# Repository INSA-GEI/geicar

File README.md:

# GeiCar Project

The GeiCar project is a project carried out by students at [INSA Toulouse](http://www.insa-toulouse.fr/fr/index.html). This project consists in developing the software of a autonomous car in order to carry out different missions. Several projects are exposed on the [official website] (https://sites.google.com/site/projetsecinsa/).

This repository is intended to provide a basis for students starting a new project on the GeiCar. The present code as well as the documentation is the result of internship carried out by [Alexis24](https://github.com/Alexix24) (Alexis Pierre Dit Lambert)

The platform is developped and maintained by :

* DI MERCURIO Sébastien
* LOMBARD Emmanuel
* MARTIN José

The projects are (or were) surpervised by:

* CHANTHERY Elodie
* DELAUTIER Sébastien
* MONTEIL Thierry
* LE BOTLAN Didier
* AURIOL Guillaume
* DI MERCURIO Sébastien

## Quick User Guide
###Turn the car on and off
* To turn on the car:
  * Toggle the red button to bring the power.
  * Press the START push button (hold it down for a short while).
  * Wait until Raspberry boot up and connect to it using its IP address (written on the board): `ssh pi@10.105.1.xx`
  * When connected start ROS subsystem using :`ros2 launch geicar_start geicar.launch.py`
  * Then, you will get a report of subsystems and be able to control the car using XBOX controler 

* To turn off the car:
	* Use the red button as a switch to turn off the power.

###Use of this repository
* First of all, [fork this repository](https://docs.github.com/en/get-started/quickstart/fork-a-repo) to get yours.
* Then, clone your fresh and new repository on your computer: `git clone https://github.com/<your id>/<your wonderful repo>`
* Have a look in "general" directory for how to connect and work with your car
* For more 'in depth' documentation on a particular subsystem, have a look in following directories:
    * raspberryPI3: Everything about raspberry setup
    * nucleoL476: Stuff about GPS-RTK and IMU
    * nucleoF103: informations on motors control, main power and ultrasonics sensors
    * jetsonNano: Directory containing info on IA, Camera and Lidar
    * simulation: if you want to setup a carla simulation environment

__warning__
You normally do not need to change firmware running in F103 and F476 boards. You main work is on the raspberry and jetson side.

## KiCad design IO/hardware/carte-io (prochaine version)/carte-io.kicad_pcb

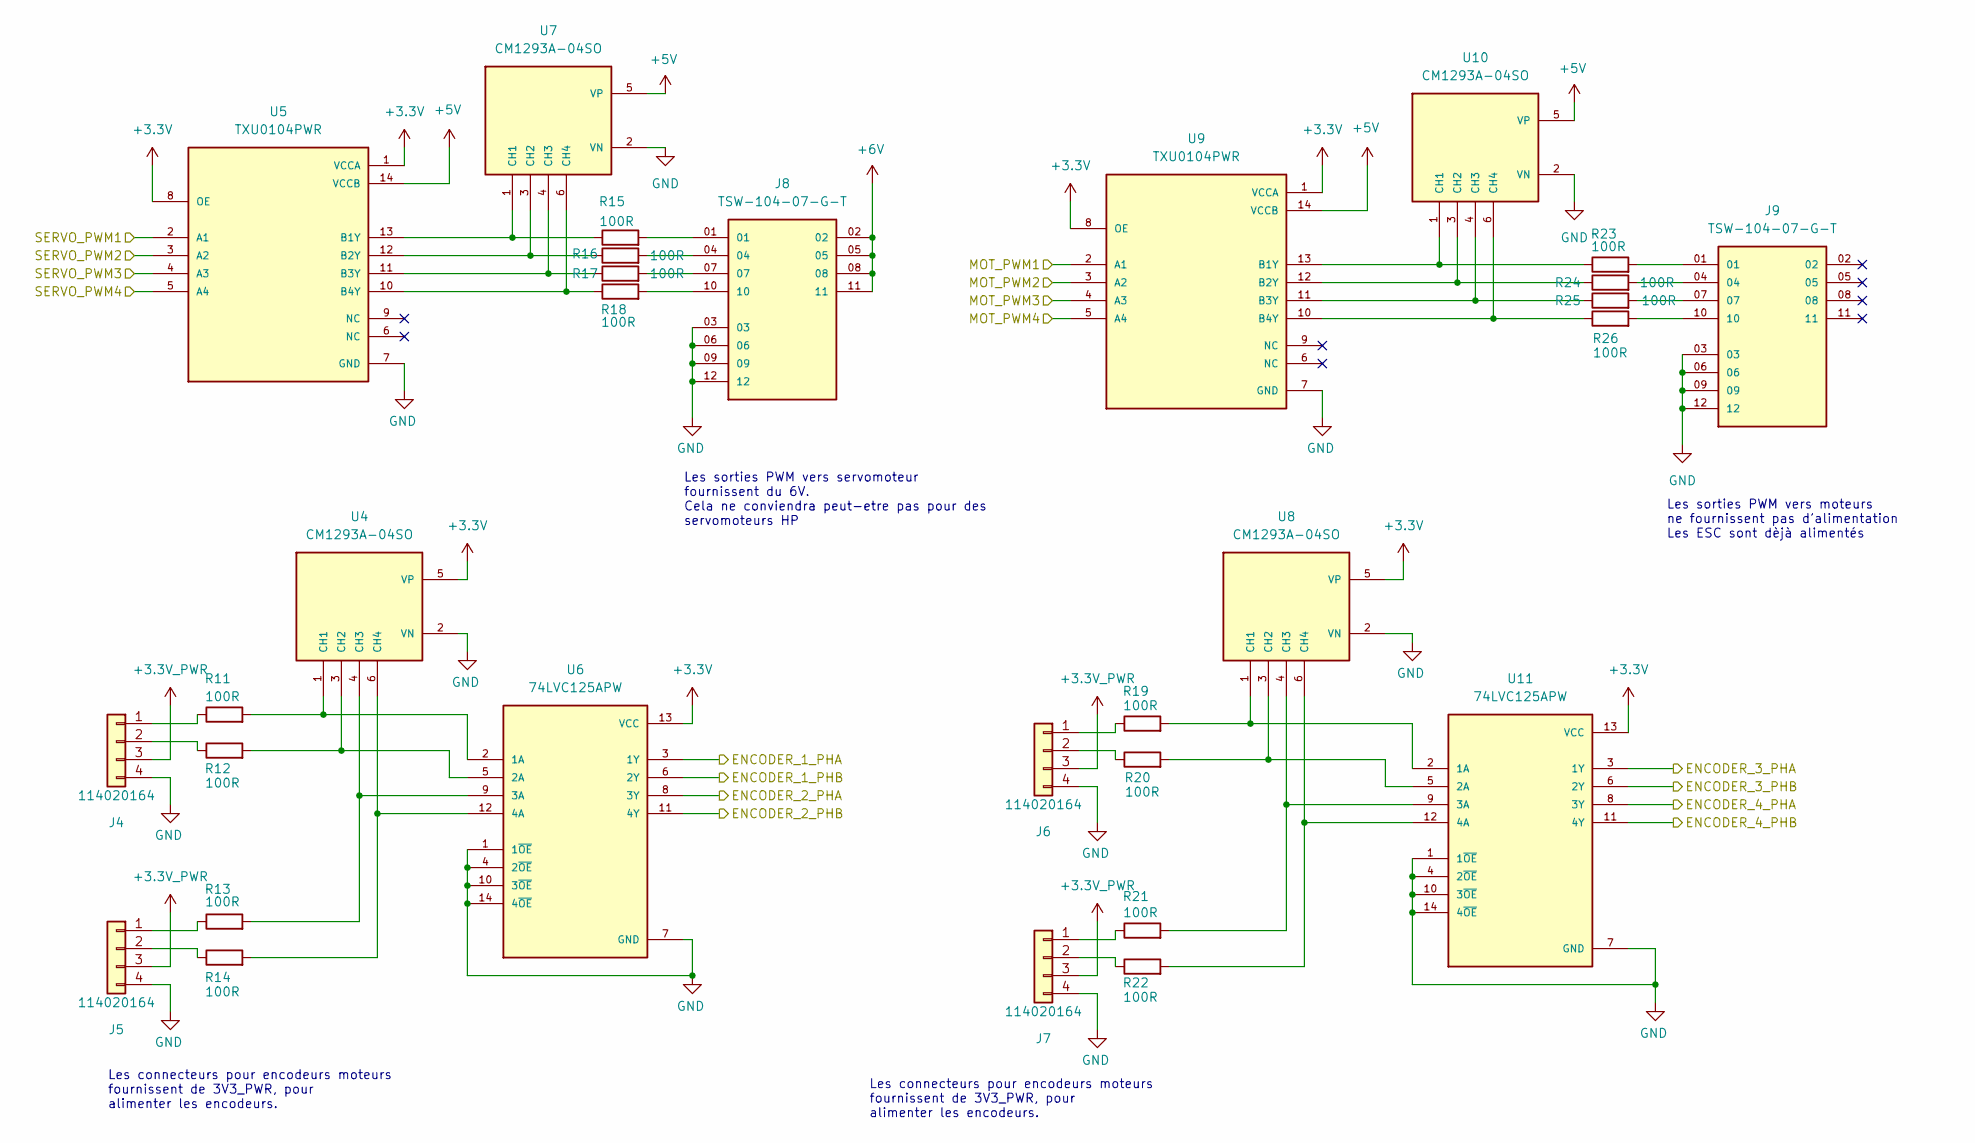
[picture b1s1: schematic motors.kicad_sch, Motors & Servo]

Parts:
J4, J5, J6, J7: 114020164; SEEEDSTUDIO_114020164
J8, J9: TSW-104-07-G-T; SAMTEC_TSW-104-07-G-T; PARTREV R
R11, R12, R13, R14, R15, R16, R17, R18, R19, R20, R21, R22, R23, R24, R25, R26: 100R; R_0805_2012Metric_Pad1.20x1.40mm_HandSolder
U4, U7, U8, U10: CM1293A-04SO; SOT95P285X140-6N
U5, U9: TXU0104PWR; SOP65P640X120-14N; PARTREV A
U6, U11: 74LVC125APW; IC_74LVC125APW; PARTREV 9

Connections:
+3.3V: U4.5 (VP), U5.1 (VCCA), U5.8 (OE), U6.13 (VCC), U8.5 (VP), U9.1 (VCCA), U9.8 (OE), U11.13 (VCC); also elsewhere on the board
+3.3V_PWR: J4.3, J5.3, J6.3, J7.3; also elsewhere on the board
+5V: U5.14 (VCCB), U7.5 (VP), U9.14 (VCCB), U10.5 (VP); also elsewhere on the board
+6V: J8.02, J8.05, J8.08, J8.11; also elsewhere on the board
/CPU/ENCODER_1_PHA: U6.3 (1Y); also elsewhere on the board
/CPU/ENCODER_1_PHB: U6.6 (2Y); also elsewhere on the board
/CPU/ENCODER_2_PHA: U6.8 (3Y); also elsewhere on the board
/CPU/ENCODER_2_PHB: U6.11 (4Y); also elsewhere on the board
/CPU/ENCODER_3_PHA: U11.3 (1Y); also elsewhere on the board
/CPU/ENCODER_3_PHB: U11.6 (2Y); also elsewhere on the board
/CPU/ENCODER_4_PHA: U11.8 (3Y); also elsewhere on the board
/CPU/ENCODER_4_PHB: U11.11 (4Y); also elsewhere on the board
/CPU/MOT_PWM1: U9.2 (A1); also elsewhere on the board
/CPU/MOT_PWM2: U9.3 (A2); also elsewhere on the board
/CPU/MOT_PWM3: U9.4 (A3); also elsewhere on the board
/CPU/MOT_PWM4: U9.5 (A4); also elsewhere on the board
/CPU/SERVO_PWM1: U5.2 (A1); also elsewhere on the board
/CPU/SERVO_PWM2N: U5.3 (A2); also elsewhere on the board
/CPU/SERVO_PWM3: U5.4 (A3); also elsewhere on the board
/CPU/SERVO_PWM4: U5.5 (A4); also elsewhere on the board
GND: J4.4, J5.4, J6.4, J7.4, J8.03, J8.06, J8.09, J8.12, J9.03, J9.06, J9.09, J9.12, U4.2 (VN), U5.7 (GND), U6.1 (1~OE), U6.4 (2~OE), U6.7 (GND), U6.10 (3~OE), U6.14 (4~OE), U7.2 (VN), U8.2 (VN), U9.7 (GND), U10.2 (VN), U11.1 (1~OE), U11.4 (2~OE), U11.7 (GND), U11.10 (3~OE), U11.14 (4~OE); also elsewhere on the board
unnamed: J4.1, R11.1
unnamed: J4.2, R12.1
unnamed: J5.1, R13.1
unnamed: J5.2, R14.1
unnamed: J6.1, R19.1
unnamed: J6.2, R20.1
unnamed: J7.1, R21.1
unnamed: J7.2, R22.1
unnamed: J8.01, R15.2
unnamed: J8.04, R16.2
unnamed: J8.07, R17.2
unnamed: J8.10, R18.2
unnamed: J9.01, R23.2
unnamed: J9.04, R24.2
unnamed: J9.07, R25.2
unnamed: J9.10, R26.2
unnamed: R11.2, U4.1 (CH1), U6.2 (1A)
unnamed: R12.2, U4.3 (CH2), U6.5 (2A)
unnamed: R13.2, U4.4 (CH3), U6.9 (3A)
unnamed: R14.2, U4.6 (CH4), U6.12 (4A)
unnamed: R15.1, U5.13 (B1Y), U7.1 (CH1)
unnamed: R16.1, U5.12 (B2Y), U7.3 (CH2)
unnamed: R17.1, U5.11 (B3Y), U7.4 (CH3)
unnamed: R18.1, U5.10 (B4Y), U7.6 (CH4)
unnamed: R23.1, U9.13 (B1Y), U10.1 (CH1)
unnamed: R24.1, U9.12 (B2Y), U10.3 (CH2)
unnamed: R25.1, U9.11 (B3Y), U10.4 (CH3)
unnamed: R26.1, U9.10 (B4Y), U10.6 (CH4)
unnamed: R19.2, U8.1 (CH1), U11.2 (1A)
unnamed: R20.2, U8.3 (CH2), U11.5 (2A)
unnamed: R21.2, U8.4 (CH3), U11.9 (3A)
unnamed: R22.2, U8.6 (CH4), U11.12 (4A)

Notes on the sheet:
Les sorties PWM vers moteurs ne fournissent pas d'alimentation Les ESC sont dèjà alimentés
Les connecteurs pour encodeurs moteurs fournissent de 3V3_PWR, pour alimenter les encodeurs.
Les sorties PWM vers servomoteur fournissent du 6V. Cela ne conviendra peut-etre pas pour des servomoteurs HP

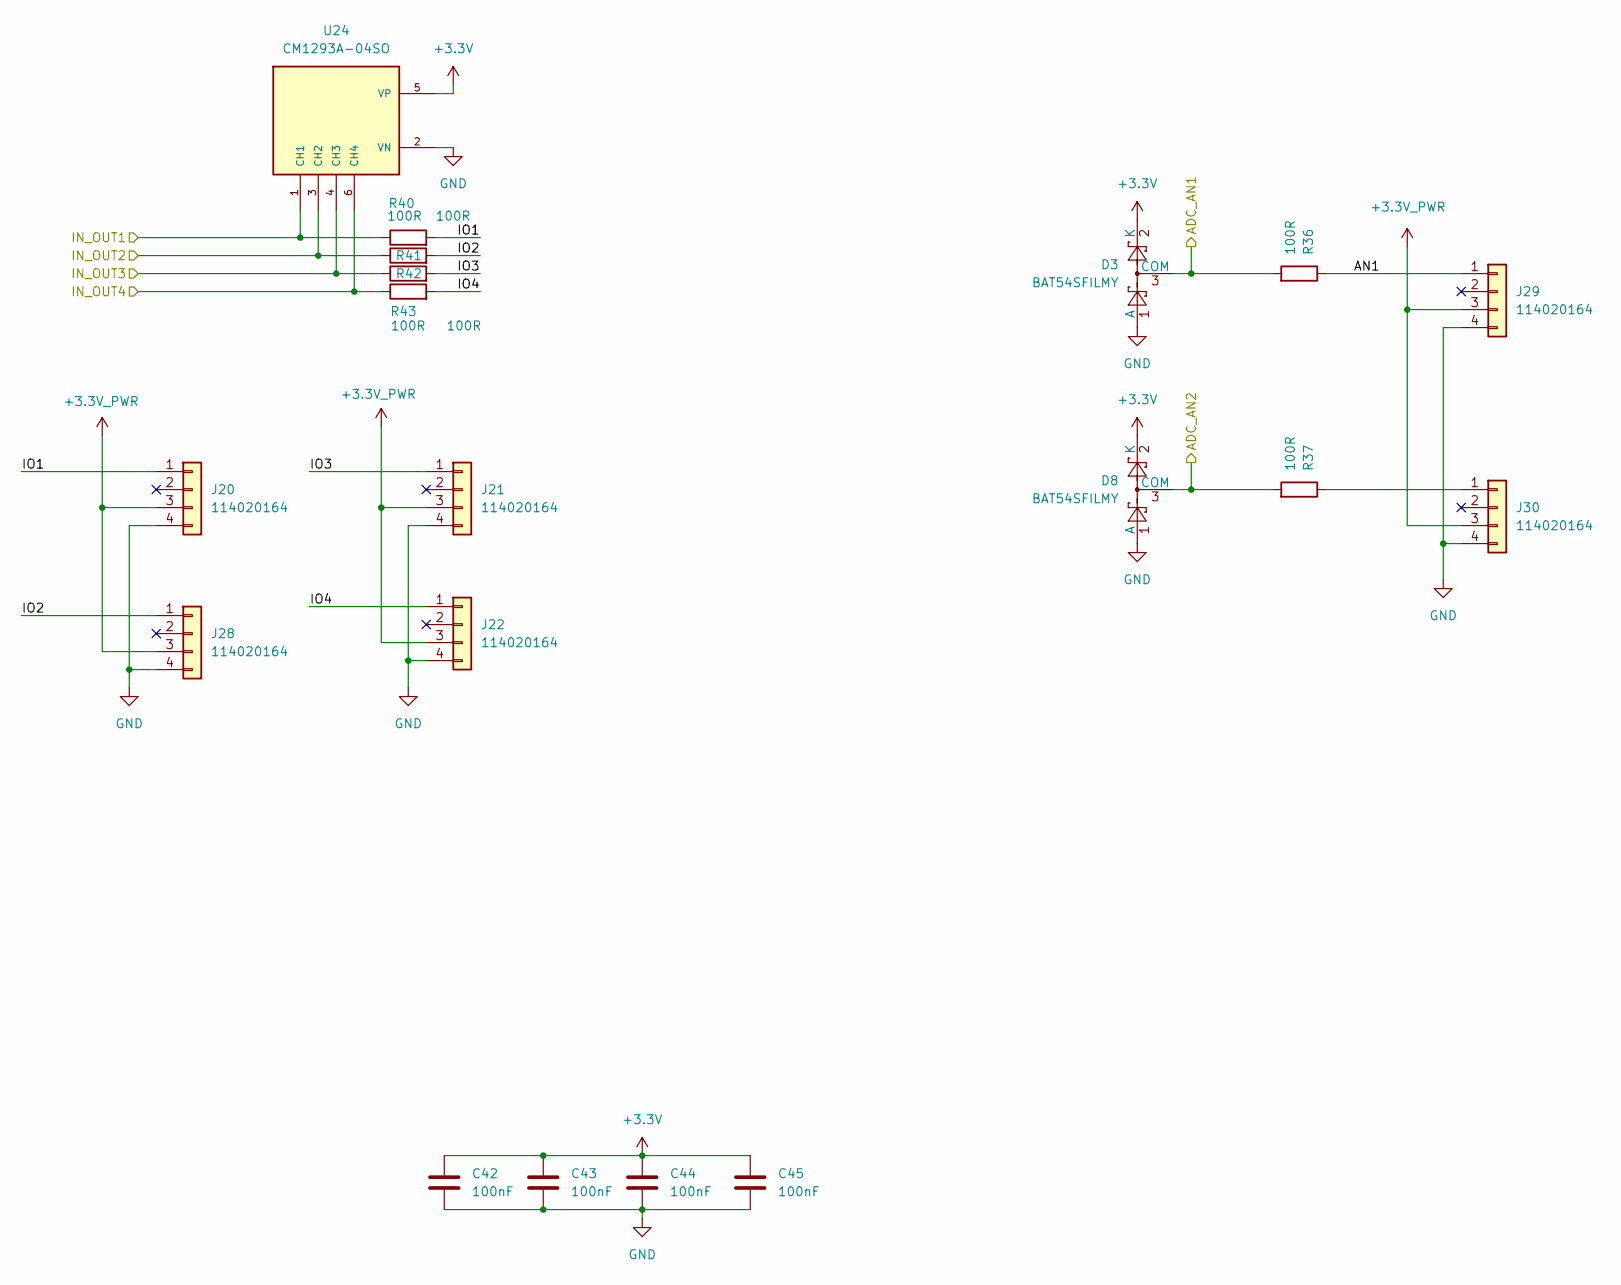
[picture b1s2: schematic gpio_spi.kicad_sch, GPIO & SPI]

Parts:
C42, C43, C44, C45: 100nF; C_0805_2012Metric_Pad1.18x1.45mm_HandSolder
D3, D8: BAT54SFILMY; SOT-23
J20, J21, J22, J28, J29, J30: 114020164; SEEEDSTUDIO_114020164
R36, R37, R40, R41, R42, R43: 100R; R_0805_2012Metric_Pad1.20x1.40mm_HandSolder
U24: CM1293A-04SO; SOT95P285X140-6N

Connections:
+3.3V: C42.1, C43.1, C44.1, C45.1, D3.2 (K), D8.2 (K), U24.5 (VP); also elsewhere on the board
+3.3V_PWR: J20.3, J21.3, J22.3, J28.3, J29.3, J30.3; also elsewhere on the board
/CPU/ADC_AN1: D3.3 (COM), R36.2; also elsewhere on the board
/CPU/ADC_AN2: D8.3 (COM), R37.2; also elsewhere on the board
/CPU/IO1: R40.1, U24.1 (CH1); also elsewhere on the board
/CPU/IO2: R41.1, U24.3 (CH2); also elsewhere on the board
/CPU/IO3: R42.1, U24.4 (CH3); also elsewhere on the board
/CPU/IO4: R43.1, U24.6 (CH4); also elsewhere on the board
/GPIO SPI GEN_PWM/AN1: J29.1, R36.1
/GPIO SPI GEN_PWM/IO1: J20.1, R40.2
/GPIO SPI GEN_PWM/IO2: J28.1, R41.2
/GPIO SPI GEN_PWM/IO3: J21.1, R42.2
/GPIO SPI GEN_PWM/IO4: J22.1, R43.2
GND: C42.2, C43.2, C44.2, C45.2, D3.1 (A), D8.1 (A), J20.4, J21.4, J22.4, J28.4, J29.4, J30.4, U24.2 (VN); also elsewhere on the board
unnamed: J30.1, R37.1

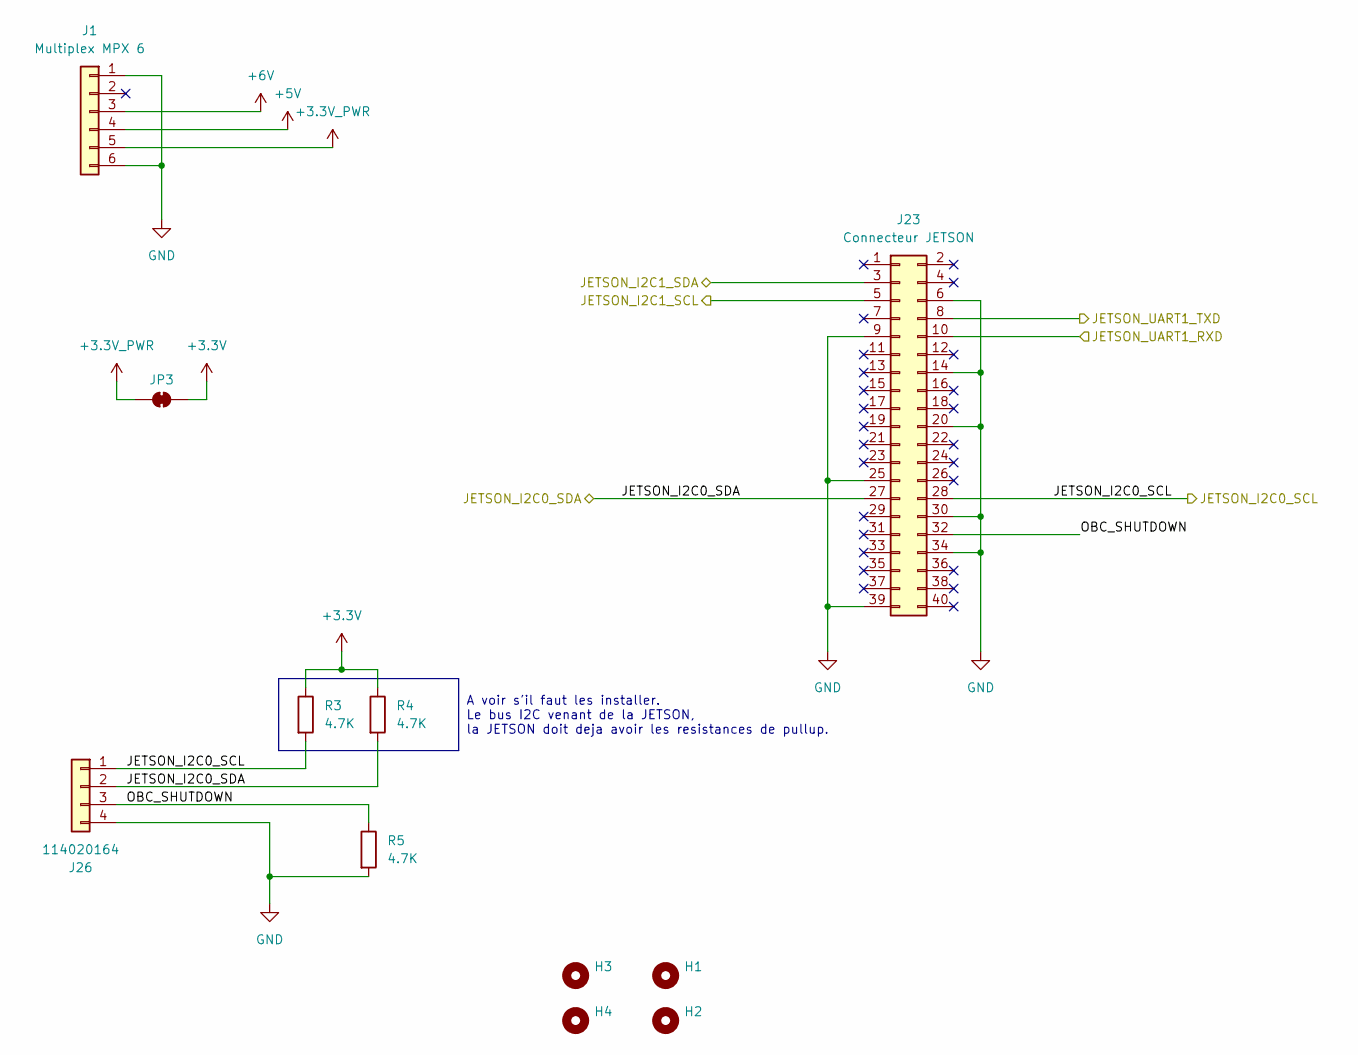
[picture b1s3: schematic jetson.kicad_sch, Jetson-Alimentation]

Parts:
H1, H2, H3, H4: MountingHole; MountingHole_3.2mm_M3
J1: Multiplex MPX 6; MPX6
J23: Connecteur JETSON; PinHeader_2x20_P2.54mm_Vertical
J26: 114020164; SEEEDSTUDIO_114020164
JP3: SolderJumper_2_Bridged; SolderJumper-2_P1.3mm_Bridged_RoundedPad1.0x1.5mm
R3, R4, R5: 4.7K; R_0805_2012Metric_Pad1.20x1.40mm_HandSolder

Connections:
+3.3V: JP3.2 (B), R3.1, R4.1; also elsewhere on the board
+3.3V_PWR: J1.5, JP3.1 (A); also elsewhere on the board
+5V: J1.4; also elsewhere on the board
+6V: J1.3; also elsewhere on the board
/CPU/COM_RXD_IO: J23.8; also elsewhere on the board
/CPU/COM_TXD_IO: J23.10; also elsewhere on the board
/Externals I2C/SENSORS_I2C_SCL: J23.5; also elsewhere on the board
/Externals I2C/SENSORS_I2C_SDA: J23.3; also elsewhere on the board
/Jetson-Alimentation/JETSON_I2C0_SCL: J23.28, J26.1, R3.2; also elsewhere on the board
/Jetson-Alimentation/JETSON_I2C0_SDA: J23.27, J26.2, R4.2; also elsewhere on the board
/Jetson-Alimentation/OBC_SHUTDOWN: J23.32, J26.3, R5.1
GND: J1.1, J1.6, J23.6, J23.9, J23.14, J23.20, J23.25, J23.30, J23.34, J23.39, J26.4, R5.2; also elsewhere on the board

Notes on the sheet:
A voir s'il faut les installer. Le bus I2C venant de la JETSON, la JETSON doit deja avoir les resistances de pullup.

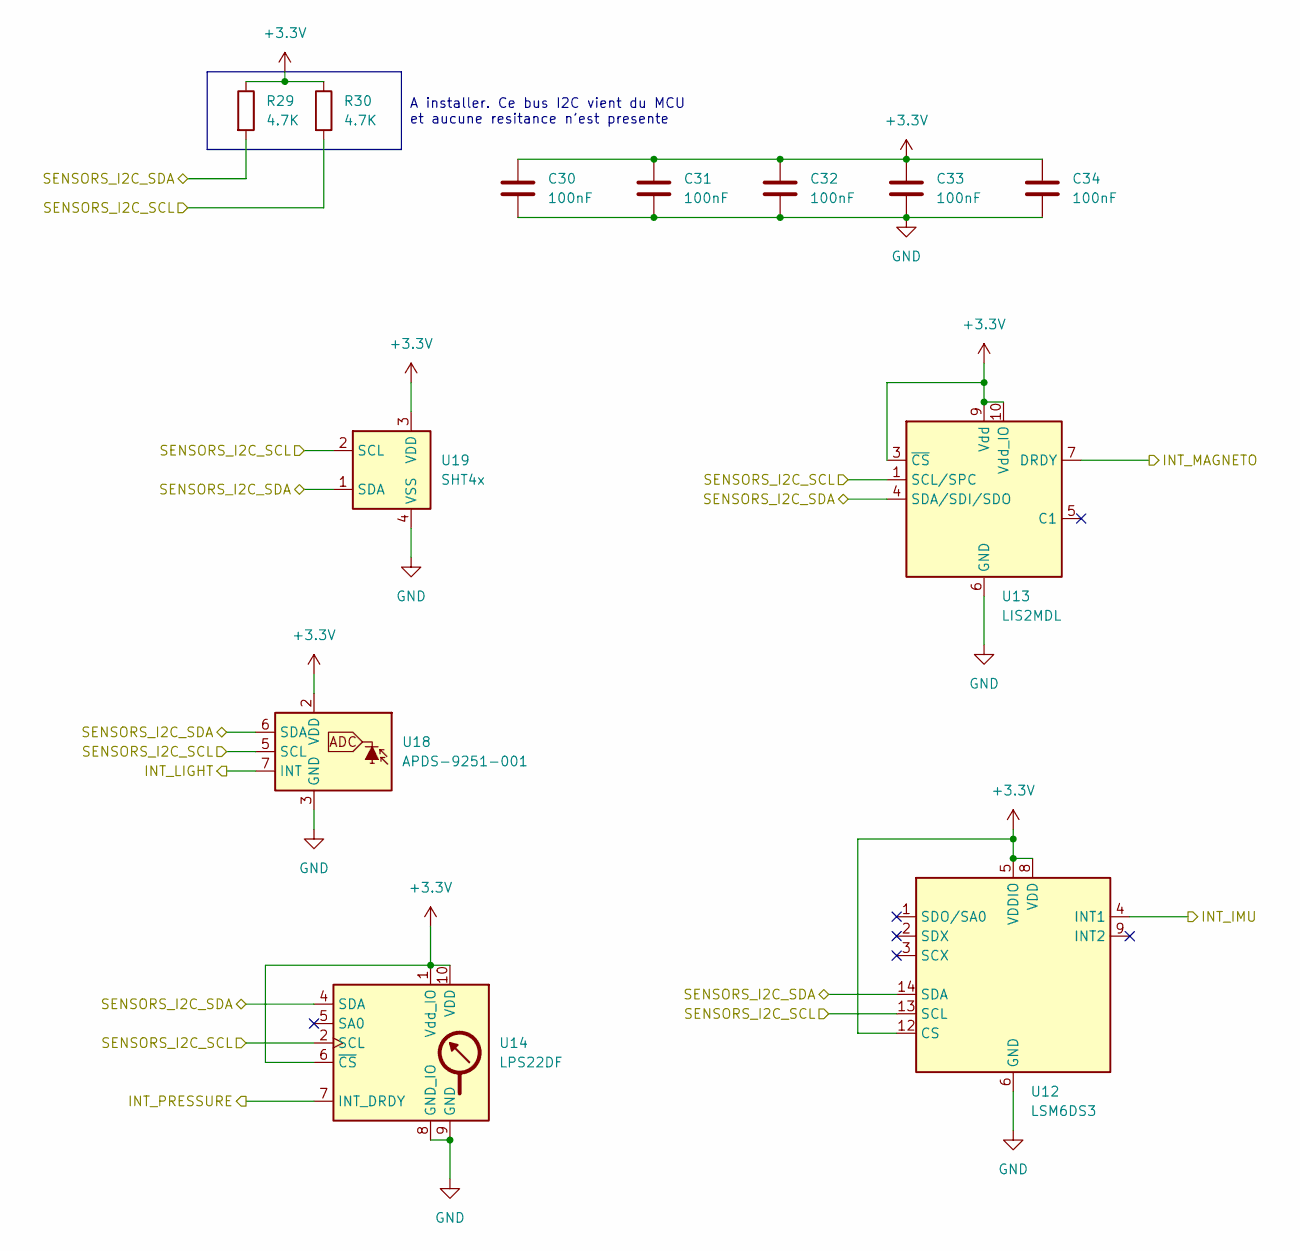
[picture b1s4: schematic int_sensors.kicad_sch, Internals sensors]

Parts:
C30, C31, C32, C33, C34: 100nF; C_0805_2012Metric_Pad1.18x1.45mm_HandSolder
R29, R30: 4.7K; R_0805_2012Metric_Pad1.20x1.40mm_HandSolder
U12: LSM6DS3; LGA-14_3x2.5mm_P0.5mm_LayoutBorder3x4y
U13: LIS2MDL; LGA-12_2x2mm_P0.5mm
U14: LPS22DF; ST_HLGA-10_2x2mm_P0.5mm_LayoutBorder3x2y
U18: APDS-9251-001; Broadcom_LGA-8_2x2mm_P0.5mm
U19: SHT4x; Sensirion_DFN-4_1.5x1.5mm_P0.8mm_SHT4x_NoCentralPad

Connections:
+3.3V: C30.1, C31.1, C32.1, C33.1, C34.1, R29.1, R30.1, U12.5 (VDDIO), U12.8 (VDD), U12.12 (CS), U13.3 (~CS), U13.9 (Vdd), U13.10 (Vdd_IO), U14.1 (Vdd_IO), U14.6 (~CS), U14.10 (VDD), U18.2 (VDD), U19.3 (VDD); also elsewhere on the board
/CPU/I2C_SCL_INT: R30.2, U12.13 (SCL), U13.1 (SCL/SPC), U14.2 (SCL), U18.5 (SCL), U19.2 (SCL); also elsewhere on the board
/CPU/I2C_SDA_INT: R29.2, U12.14 (SDA), U13.4 (SDA/SDI/SDO), U14.4 (SDA), U18.6 (SDA), U19.1 (SDA); also elsewhere on the board
/CPU/INT_IMU: U12.4 (INT1); also elsewhere on the board
/CPU/INT_LIGHT: U18.7 (INT); also elsewhere on the board
/CPU/INT_MAGNETO: U13.7 (DRDY); also elsewhere on the board
/CPU/INT_PRESSURE: U14.7 (INT_DRDY); also elsewhere on the board
GND: C30.2, C31.2, C32.2, C33.2, C34.2, U12.6 (GND), U12.7 (GND), U13.6 (GND), U13.8 (GND), U14.3 (GND), U14.8 (GND_IO), U14.9 (GND), U18.3 (GND), U19.4 (VSS); also elsewhere on the board

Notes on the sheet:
A installer. Ce bus I2C vient du MCU et aucune resitance n'est presente

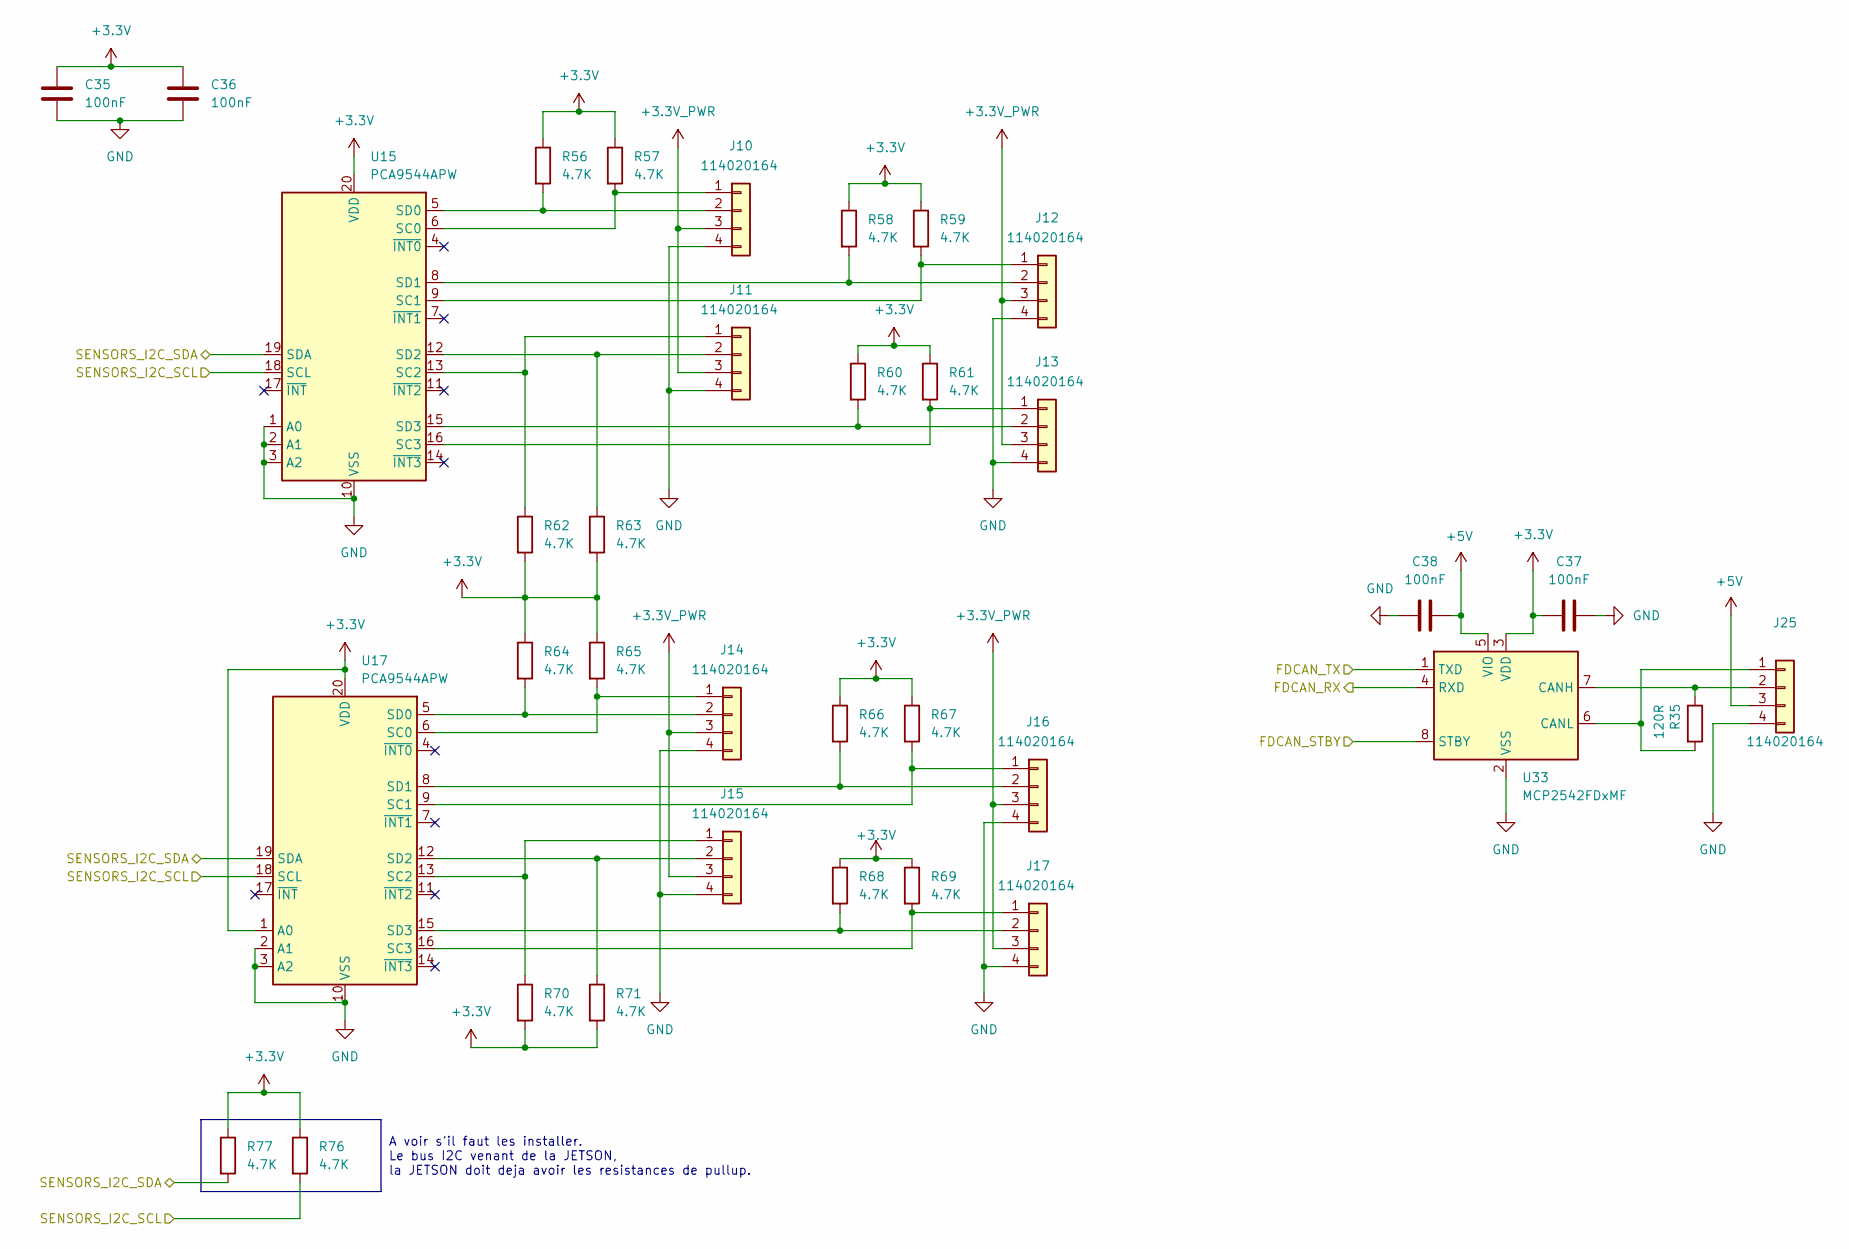
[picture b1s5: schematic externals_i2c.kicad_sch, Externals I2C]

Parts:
C35, C36, C37, C38: 100nF; C_0805_2012Metric_Pad1.18x1.45mm_HandSolder
J10, J11, J12, J13, J14, J15, J16, J17, J25: 114020164; SEEEDSTUDIO_114020164
R35: 120R; R_0805_2012Metric_Pad1.20x1.40mm_HandSolder
R56, R57, R58, R59, R60, R61, R62, R63, R64, R65, R66, R67, R68, R69, R70, R71, R76, R77: 4.7K; R_0805_2012Metric_Pad1.20x1.40mm_HandSolder
U15, U17: PCA9544APW; TSSOP-20_4.4x6.5mm_P0.65mm
U33: MCP2542FDxMF; DFN-8-1EP_3x3mm_P0.65mm_EP1.55x2.4mm

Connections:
+3.3V: C35.1, C36.1, C37.1, R56.1, R57.1, R58.1, R59.1, R60.1, R61.1, R62.2, R63.2, R64.1, R65.1, R66.1, R67.1, R68.1, R69.1, R70.2, R71.2, R76.1, R77.1, U15.20 (VDD), U17.1 (A0), U17.20 (VDD), U33.3 (VDD); also elsewhere on the board
+3.3V_PWR: J10.3, J11.3, J12.3, J13.3, J14.3, J15.3, J16.3, J17.3; also elsewhere on the board
+5V: C38.2, J25.3, U33.5 (VIO); also elsewhere on the board
/CPU/FDCAN1_RX: U33.4 (RXD); also elsewhere on the board
/CPU/FDCAN1_TX: U33.1 (TXD); also elsewhere on the board
/CPU/FDCAN_STBY: U33.8 (STBY); also elsewhere on the board
/Externals I2C/SENSORS_I2C_SCL: R76.2, U15.18 (SCL), U17.18 (SCL); also elsewhere on the board
/Externals I2C/SENSORS_I2C_SDA: R77.2, U15.19 (SDA), U17.19 (SDA); also elsewhere on the board
GND: C35.2, C36.2, C37.2, C38.1, J10.4, J11.4, J12.4, J13.4, J14.4, J15.4, J16.4, J17.4, J25.4, U15.1 (A0), U15.2 (A1), U15.3 (A2), U15.10 (VSS), U17.2 (A1), U17.3 (A2), U17.10 (VSS), U33.2 (VSS), U33.9 (VSS); also elsewhere on the board
unnamed: J10.1, R57.2, U15.6 (SC0)
unnamed: J10.2, R56.2, U15.5 (SD0)
unnamed: J11.1, R62.1, U15.13 (SC2)
unnamed: J11.2, R63.1, U15.12 (SD2)
unnamed: J12.1, R59.2, U15.9 (SC1)
unnamed: J12.2, R58.2, U15.8 (SD1)
unnamed: J13.1, R61.2, U15.16 (SC3)
unnamed: J13.2, R60.2, U15.15 (SD3)
unnamed: J14.1, R65.2, U17.6 (SC0)
unnamed: J14.2, R64.2, U17.5 (SD0)
unnamed: J15.1, R70.1, U17.13 (SC2)
unnamed: J15.2, R71.1, U17.12 (SD2)
unnamed: J16.1, R67.2, U17.9 (SC1)
unnamed: J16.2, R66.2, U17.8 (SD1)
unnamed: J17.1, R69.2, U17.16 (SC3)
unnamed: J17.2, R68.2, U17.15 (SD3)
unnamed: J25.1, R35.2, U33.6 (CANL)
unnamed: J25.2, R35.1, U33.7 (CANH)

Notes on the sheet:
A voir s'il faut les installer. Le bus I2C venant de la JETSON, la JETSON doit deja avoir les resistances de pullup.

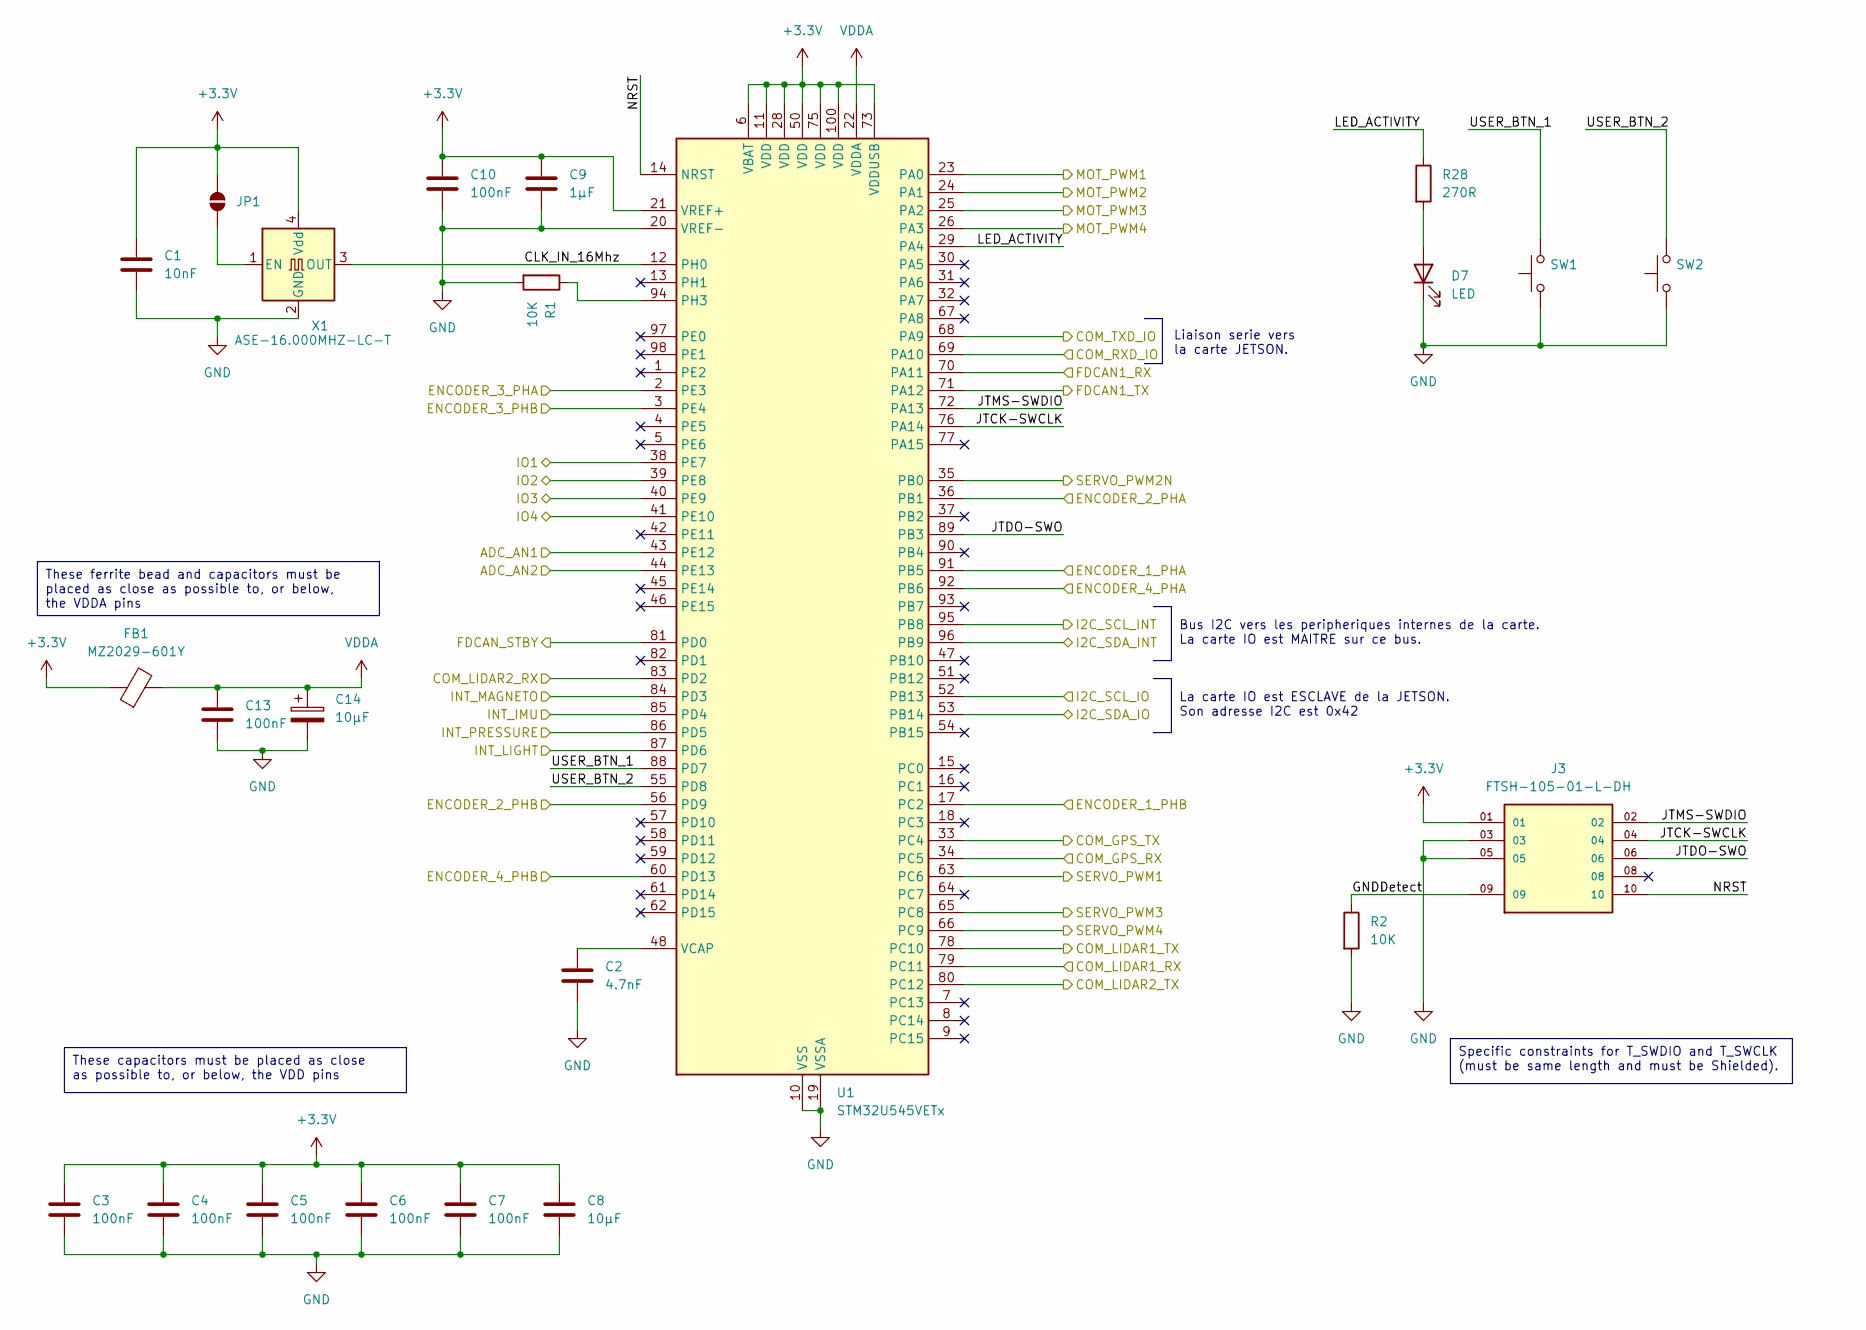
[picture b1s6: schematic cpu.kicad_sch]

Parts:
C1: 10nF; C_0805_2012Metric_Pad1.18x1.45mm_HandSolder
C2: 4.7nF; C_0805_2012Metric_Pad1.18x1.45mm_HandSolder
C3, C4, C5, C6, C7, C10: 100nF; C_0805_2012Metric_Pad1.18x1.45mm_HandSolder
C8: 10µF; C_0805_2012Metric_Pad1.18x1.45mm_HandSolder
C9: 1µF; C_0805_2012Metric_Pad1.18x1.45mm_HandSolder
C13: 100nF; C_0805_2012Metric
C14: 10µF; C_1206_3216Metric
D7: LED; LED_0805_2012Metric
FB1: MZ2029-601Y; L_Eaton_MCL2012V1
J3: FTSH-105-01-L-DH; SAMTEC_FTSH-105-01-L-DH; PARTREV H
JP1: SolderJumper_2_Open; SolderJumper-2_P1.3mm_Open_RoundedPad1.0x1.5mm
R1, R2: 10K; R_0805_2012Metric_Pad1.20x1.40mm_HandSolder
R28: 270R; R_0805_2012Metric_Pad1.20x1.40mm_HandSolder
SW1, SW2: SW_Push; 218250270
U1: STM32U545VETx; LQFP-100_14x14mm_P0.5mm
X1: ASE-16.000MHZ-LC-T; Oscillator_SMD_Abracon_ASE-4Pin_3.2x2.5mm

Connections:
+3.3V: C1.1, C3.1, C4.1, C5.1, C6.1, C7.1, C8.1, C9.1, C10.1, FB1.1, J3.01, JP1.2 (B), U1.6 (VBAT), U1.11 (VDD), U1.21 (VREF+), U1.28 (VDD), U1.50 (VDD), U1.73 (VDDUSB), U1.75 (VDD), U1.100 (VDD), X1.4 (Vdd); also elsewhere on the board
/CPU/ADC_AN1: U1.43 (PE12); also elsewhere on the board
/CPU/ADC_AN2: U1.44 (PE13); also elsewhere on the board
/CPU/CLK_IN_16Mhz: U1.12 (PH0), X1.3 (OUT)
/CPU/COM_GPS_RX: U1.34 (PC5); also elsewhere on the board
/CPU/COM_GPS_TX: U1.33 (PC4); also elsewhere on the board
/CPU/COM_LIDAR1_RX: U1.79 (PC11); also elsewhere on the board
/CPU/COM_LIDAR1_TX: U1.78 (PC10); also elsewhere on the board
/CPU/COM_LIDAR2_RX: U1.83 (PD2); also elsewhere on the board
/CPU/COM_LIDAR2_TX: U1.80 (PC12); also elsewhere on the board
/CPU/COM_RXD_IO: U1.69 (PA10); also elsewhere on the board
/CPU/COM_TXD_IO: U1.68 (PA9); also elsewhere on the board
/CPU/ENCODER_1_PHA: U1.91 (PB5); also elsewhere on the board
/CPU/ENCODER_1_PHB: U1.17 (PC2); also elsewhere on the board
/CPU/ENCODER_2_PHA: U1.36 (PB1); also elsewhere on the board
/CPU/ENCODER_2_PHB: U1.56 (PD9); also elsewhere on the board
/CPU/ENCODER_3_PHA: U1.2 (PE3); also elsewhere on the board
/CPU/ENCODER_3_PHB: U1.3 (PE4); also elsewhere on the board
/CPU/ENCODER_4_PHA: U1.92 (PB6); also elsewhere on the board
/CPU/ENCODER_4_PHB: U1.60 (PD13); also elsewhere on the board
/CPU/FDCAN1_RX: U1.70 (PA11); also elsewhere on the board
/CPU/FDCAN1_TX: U1.71 (PA12); also elsewhere on the board
/CPU/FDCAN_STBY: U1.81 (PD0); also elsewhere on the board
/CPU/GNDDetect: J3.09, R2.1
/CPU/I2C_SCL_INT: U1.95 (PB8); also elsewhere on the board
/CPU/I2C_SDA_INT: U1.96 (PB9); also elsewhere on the board
/CPU/INT_IMU: U1.85 (PD4); also elsewhere on the board
/CPU/INT_LIGHT: U1.87 (PD6); also elsewhere on the board
/CPU/INT_MAGNETO: U1.84 (PD3); also elsewhere on the board
/CPU/INT_PRESSURE: U1.86 (PD5); also elsewhere on the board
/CPU/IO1: U1.38 (PE7); also elsewhere on the board
/CPU/IO2: U1.39 (PE8); also elsewhere on the board
/CPU/IO3: U1.40 (PE9); also elsewhere on the board
/CPU/IO4: U1.41 (PE10); also elsewhere on the board
/CPU/JTCK-SWCLK: J3.04, U1.76 (PA14)
/CPU/JTDO-SWO: J3.06, U1.89 (PB3)
/CPU/JTMS-SWDIO: J3.02, U1.72 (PA13)
/CPU/LED_ACTIVITY: R28.1, U1.29 (PA4)
/CPU/MOT_PWM1: U1.23 (PA0); also elsewhere on the board
/CPU/MOT_PWM2: U1.24 (PA1); also elsewhere on the board
/CPU/MOT_PWM3: U1.25 (PA2); also elsewhere on the board
/CPU/MOT_PWM4: U1.26 (PA3); also elsewhere on the board
/CPU/NRST: J3.10, U1.14 (NRST)
/CPU/SERVO_PWM1: U1.63 (PC6); also elsewhere on the board
/CPU/SERVO_PWM2N: U1.35 (PB0); also elsewhere on the board
/CPU/SERVO_PWM3: U1.65 (PC8); also elsewhere on the board
/CPU/SERVO_PWM4: U1.66 (PC9); also elsewhere on the board
/CPU/USER_BTN_1: SW1.2, U1.88 (PD7)
/CPU/USER_BTN_2: SW2.2, U1.55 (PD8)
/Jetson-Alimentation/JETSON_I2C0_SCL: U1.52 (PB13); also elsewhere on the board
/Jetson-Alimentation/JETSON_I2C0_SDA: U1.53 (PB14); also elsewhere on the board
GND: C1.2, C2.2, C3.2, C4.2, C5.2, C6.2, C7.2, C8.2, C9.2, C10.2, C13.2, C14.2, D7.1 (K), J3.03, J3.05, R1.2, R2.2, SW1.1, SW2.1, U1.10 (VSS), U1.19 (VSSA), U1.20 (VREF-), U1.27 (VSS), U1.49 (VSS), U1.74 (VSS), U1.99 (VSS), X1.2 (GND); also elsewhere on the board
unnamed: D7.2 (A), R28.2
unnamed: JP1.1 (A), X1.1 (EN)
unnamed: R1.1, U1.94 (PH3)
unnamed: C2.1, U1.48 (VCAP)
VDDA: C13.1, C14.1, FB1.2, U1.22 (VDDA)

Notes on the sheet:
These capacitors must be placed as close as possible to, or below, the VDD pins
These ferrite bead and capacitors must be placed as close as possible to, or below, the VDDA pins
Specific constraints for T_SWDIO and T_SWCLK (must be same length and must be Shielded).
Liaison serie vers la carte JETSON.
La carte IO est ESCLAVE de la JETSON. Son adresse I2C est 0x42
Bus I2C vers les peripheriques internes de la carte. La carte IO est MAITRE sur ce bus.
